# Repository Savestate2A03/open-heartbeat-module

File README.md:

# Open Heartbeat Module
An open source GameCube Controller heartbeat module.

Ordering guide can be found in the [GitHub release](https://github.com/Savestate2A03/open-heartbeat-module/releases).

# Images

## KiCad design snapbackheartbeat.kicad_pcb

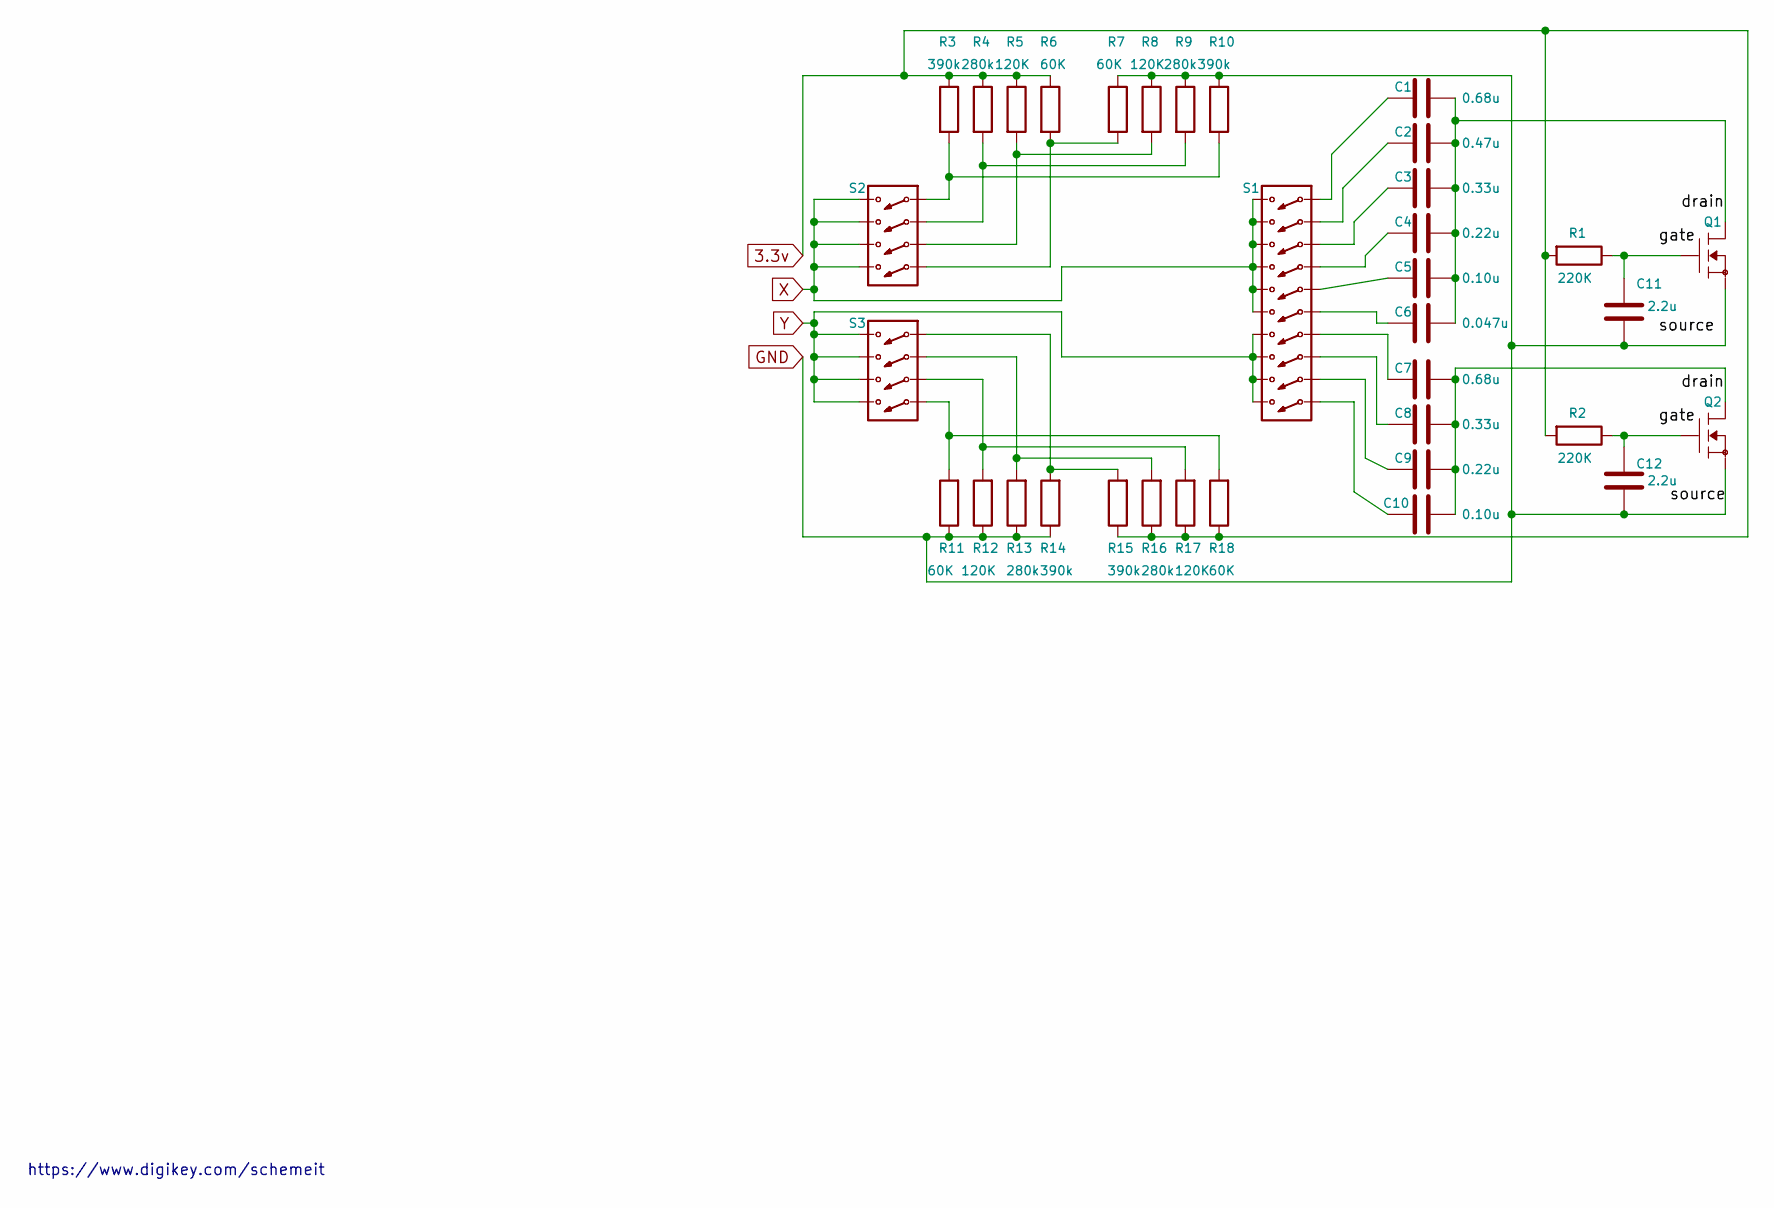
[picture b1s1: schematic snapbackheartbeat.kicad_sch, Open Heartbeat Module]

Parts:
C1, C7: 0.68u; C_0402_1005Metric
C2: 0.47u; C_0402_1005Metric
C3, C8: 0.33u; C_0402_1005Metric
C4, C9: 0.22u; C_0402_1005Metric
C5, C10: 0.10u; C_0402_1005Metric
C6: 0.047u; C_0402_1005Metric
C11, C12: 2.2u; C_0402_1005Metric
Q1, Q2: SOT-323_SC-70
R1, R2: 220K; R_0402_1005Metric
R3, R10, R14, R15: 390k; R_0402_1005Metric
R4, R9, R13, R16: 280k; R_0402_1005Metric
R5, R8, R12, R17: 120K; R_0402_1005Metric
R6, R7, R11, R18: 60K; R_0402_1005Metric
S1: SW_DIP_SPSTx10_Slide_Copal_CHS-10B_W7.62mm_P1.27mm
S2, S3: SW_DIP_SPSTx04_Slide_Copal_CHS-04B_W7.62mm_P1.27mm

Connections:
3.3v: R1.2, R2.2, R3.1, R4.1, R5.1, R6.1, R15.1, R16.1, R17.1, R18.1; also elsewhere on the board
GND: C11.2, C12.2, Q1.2, Q2.2, R7.1, R8.1, R9.1, R10.1, R11.1, R12.1, R13.1, R14.1; also elsewhere on the board
unnamed: C1.1, C2.1, C3.1, C4.1, C5.1, C6.1, Q1.1
unnamed: C1.2, S1.10
unnamed: C2.2, S1.9
unnamed: C3.2, S1.8
unnamed: C4.2, S1.7
unnamed: C5.2, S1.6
unnamed: C6.2, S1.5
unnamed: C7.2, S1.4
unnamed: C8.2, S1.3
unnamed: C9.2, S1.2
unnamed: C7.1, C8.1, C9.1, C10.1, Q2.1
unnamed: C10.2, S1.1
unnamed: C11.1, Q1.3, R1.1
unnamed: C12.1, Q2.3, R2.1
unnamed: R4.2, R9.2, S2.3
unnamed: R5.2, R8.2, S2.2
unnamed: R6.2, R7.2, S2.1
unnamed: R3.2, R10.2, S2.4
unnamed: R11.2, R18.2, S3.1
unnamed: R12.2, R17.2, S3.2
unnamed: R13.2, R16.2, S3.3
unnamed: R14.2, R15.2, S3.4
X: S1.11, S1.12, S1.13, S1.14, S1.15, S1.16, S2.5, S2.6, S2.7, S2.8; also elsewhere on the board
Y: S1.17, S1.18, S1.19, S1.20, S3.5, S3.6, S3.7, S3.8; also elsewhere on the board

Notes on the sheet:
https://www.digikey.com/schemeit

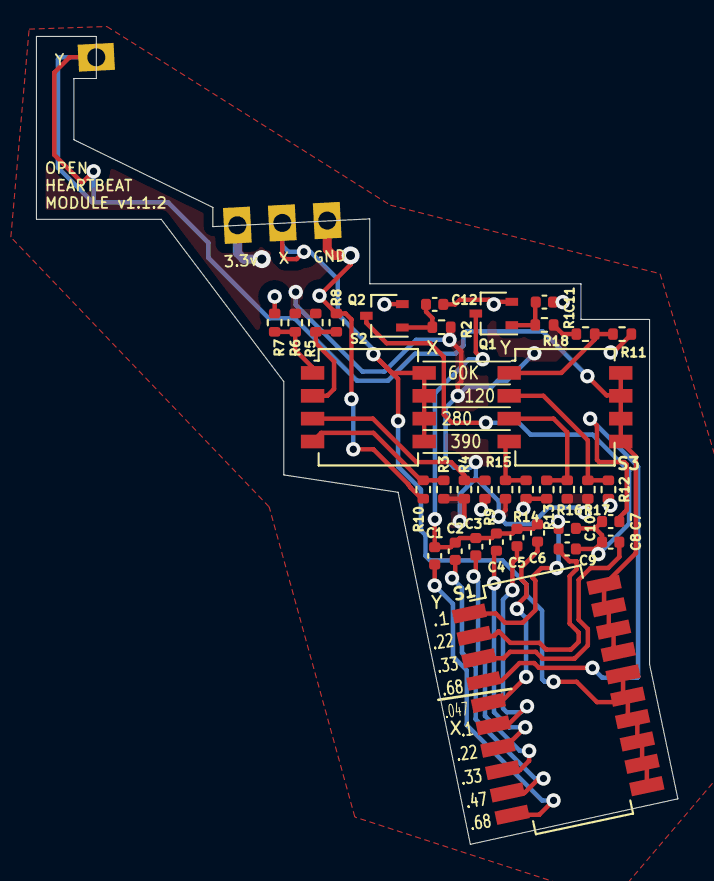
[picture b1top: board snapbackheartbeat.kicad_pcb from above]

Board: 2 copper layers, 35.6 x 44.9 mm, 36 parts (1 on the bottom side), 26 nets.

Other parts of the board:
U2: 2x DRV5053CAQLPGM Hall Effect Sensors; GCC_Stickbox_2

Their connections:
3.3v: U2.15 (P1XV); also elsewhere on the board
GND: U2.13 (P1XG); also elsewhere on the board
X: U2.14 (P1XS); also elsewhere on the board
Y: U2.17 (P1YS); also elsewhere on the board

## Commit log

2022-10-26 add kicad files
2022-11-06 fixed mosfet pinout and 3.3 to gate
2022-11-06 make pcb work with noncasstelated edges
2022-11-06 add version number
2022-11-07 shrink corner a bit
2022-11-07 update version number
